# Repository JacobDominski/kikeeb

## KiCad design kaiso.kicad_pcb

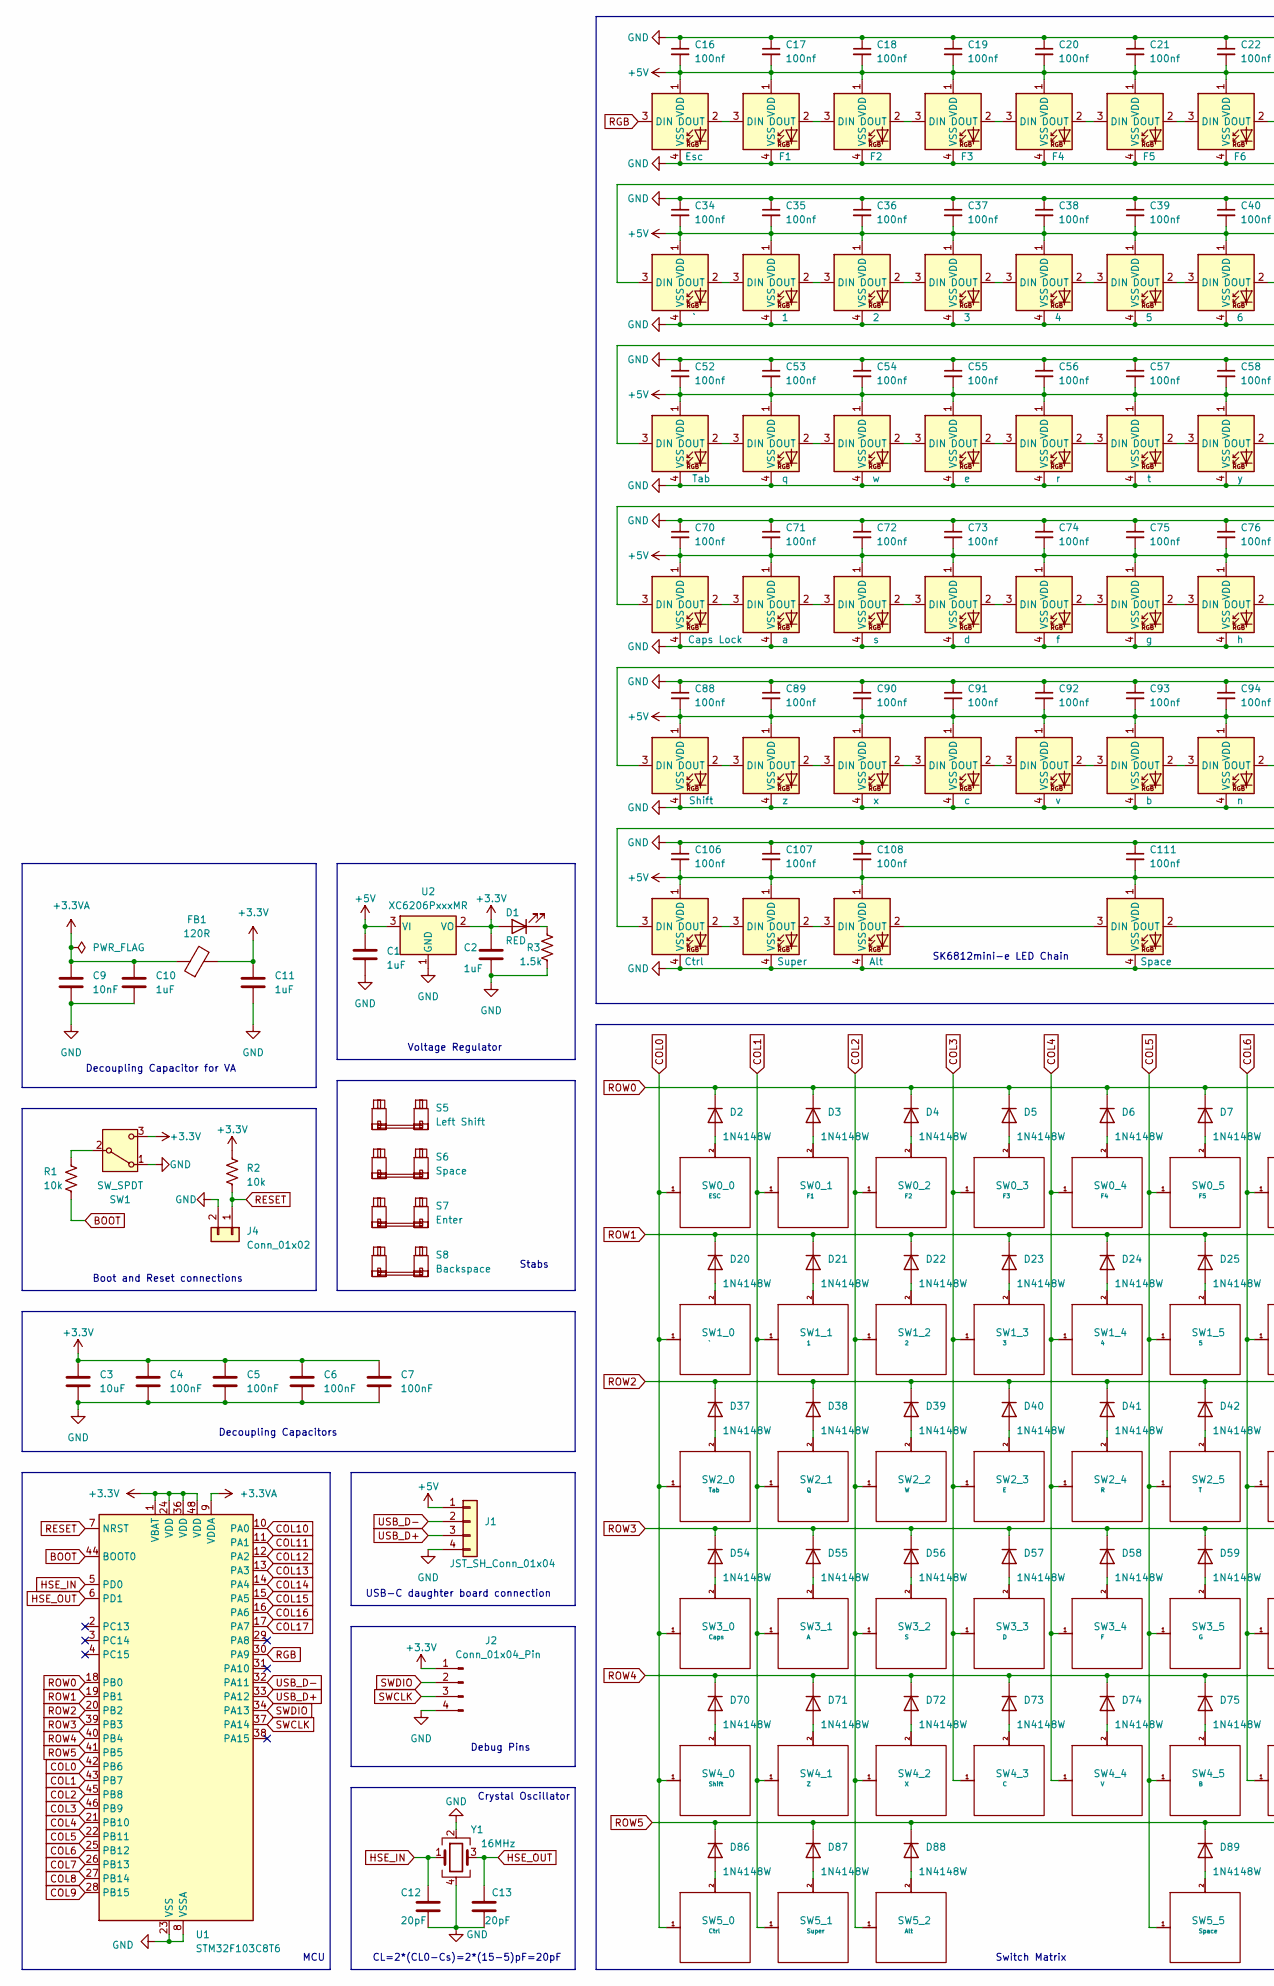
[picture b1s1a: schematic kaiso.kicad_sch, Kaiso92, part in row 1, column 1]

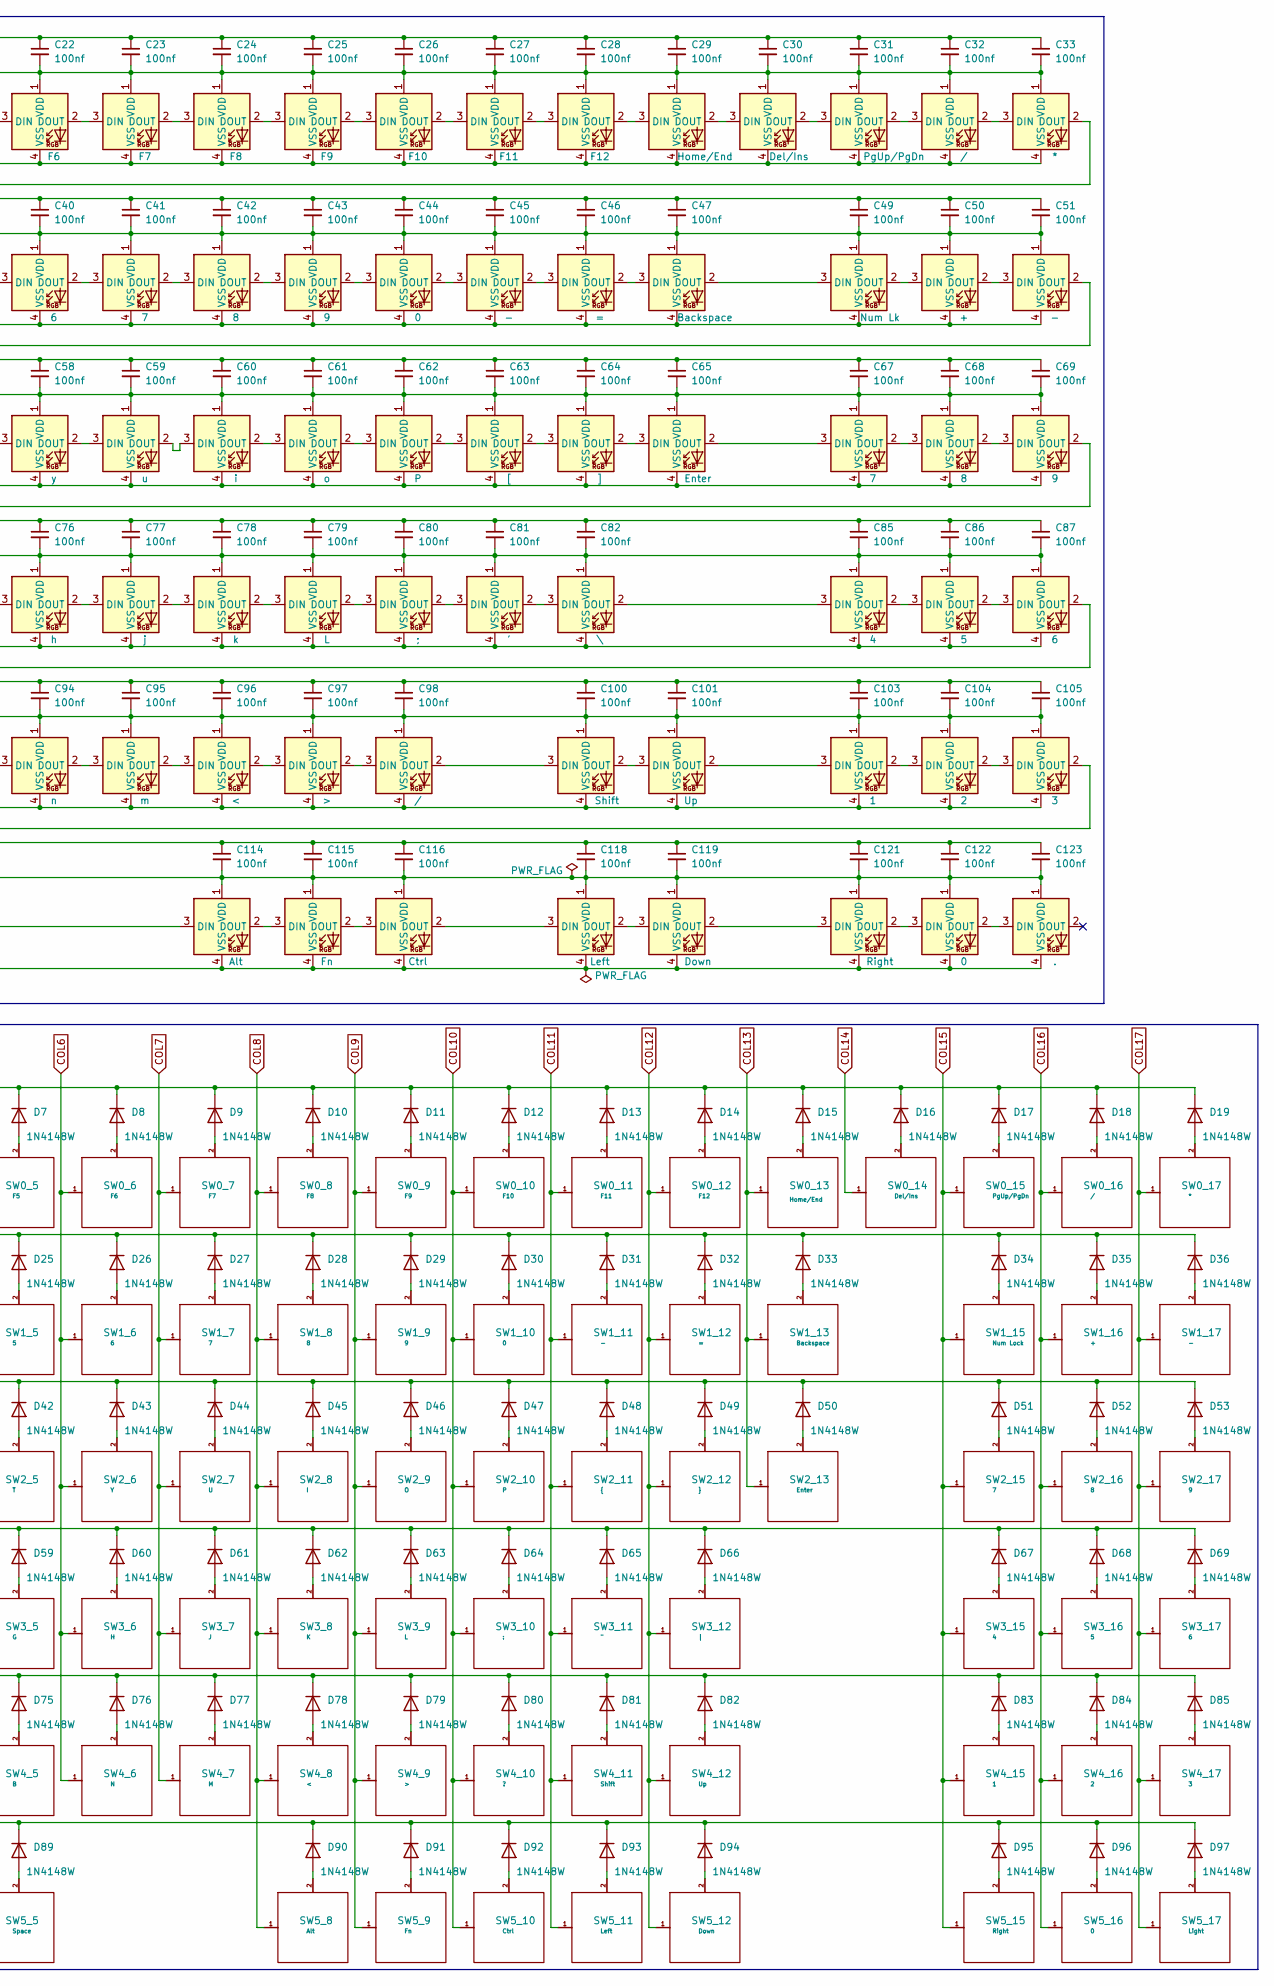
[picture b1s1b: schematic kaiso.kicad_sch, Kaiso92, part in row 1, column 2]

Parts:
C1, C2, C10, C11: 1uF; C_0402_1005Metric
C3: 10uF; C_0603_1608Metric
C4, C5, C6, C7: 100nF; C_0402_1005Metric
C9: 10nF; C_0603_1608Metric
C12, C13: 20pF; C_0201_0603Metric
C16, C17, C18, C19, C20, C21, C22, C23, C24, C25, C26, C27, C28, C29, C30, C31, C32, C33, C34, C35, C36, C37, C38, C39, C40, C41, C42, C43, C44, C45, C46, C47, C49, C50, C51, C52, C53, C54, C55, C56, C57, C58, C59, C60, C61, C62, C63, C64, C65, C67, C68, C69, C70, C71, C72, C73, C74, C75, C76, C77, C78, C79, C80, C81, C82, C85, C86, C87, C88, C89, C90, C91, C92, C93, C94, C95, C96, C97, C98, C100, C101, C103, C104, C105, C106, C107, C108, C111, C114, C115, C116, C118, C119, C121, C122, C123: 100nf; C_0402_1005Metric
D1: RED; LED_0603_1608Metric
D2, D3, D4, D5, D6, D7, D8, D9, D10, D11, D12, D13, D14, D15, D16, D17, D18, D19, D20, D21, D22, D23, D24, D25, D26, D27, D28, D29, D30, D31, D32, D33, D34, D35, D36, D37, D38, D39, D40, D41, D42, D43, D44, D45, D46, D47, D48, D49, D50, D51, D52, D53, D54, D55, D56, D57, D58, D59, D60, D61, D62, D63, D64, D65, D66, D67, D68, D69, D70, D71, D72, D73, D74, D75, D76, D77, D78, D79, D80, D81, D82, D83, D84, D85, D86, D87, D88, D89, D90, D91, D92, D93, D94, D95, D96, D97: 1N4148W; D_SOD-123
FB1: 120R; L_0603_1608Metric
J1: JST_SH_Conn_01x04; JST_SH_SM04B-SRSS-TB_1x04-1MP_P1.00mm_Horizontal
J2: Conn_01x04_Pin; PinHeader_1x04_P2.54mm_Vertical
J4: Conn_01x02; PinHeader_1x02_P2.54mm_Vertical
LED1: Esc; LED_MX_6028R
LED2: F1; LED_MX_6028R
LED3: F2; LED_MX_6028R
LED4: F3; LED_MX_6028R
LED5: F4; LED_MX_6028R
LED6: F5; LED_MX_6028R
LED7: F6; LED_MX_6028R
LED8: F7; LED_MX_6028R
LED9: F8; LED_MX_6028R
LED10: F9; LED_MX_6028R
LED11: F10; LED_MX_6028R
LED12: F11; LED_MX_6028R
LED13: F12; LED_MX_6028R
LED14: Home/End; LED_MX_6028R
LED15: Del/Ins; LED_MX_6028R
LED16: PgUp/PgDn; LED_MX_6028R
LED17, LED83: /; LED_MX_6028R
LED18: *; LED_MX_6028R
LED19: `; LED_MX_6028R
LED20, LED88: 1; LED_MX_6028R
LED21, LED89: 2; LED_MX_6028R
LED22, LED90: 3; LED_MX_6028R
LED23, LED70: 4; LED_MX_6028R
LED24, LED71: 5; LED_MX_6028R
LED25, LED72: 6; LED_MX_6028R
LED26, LED52: 7; LED_MX_6028R
LED27, LED53: 8; LED_MX_6028R
LED28, LED54: 9; LED_MX_6028R
LED29, LED107: 0; LED_MX_6028R
LED30, LED36: -; LED_MX_6028R
LED31: =; LED_MX_6028R
LED32: Backspace; LED_MX_6028R
LED34: Num Lk; LED_MX_6028R
LED35: +; LED_MX_6028R
LED37: Tab; LED_MX_6028R
LED38: q; LED_MX_6028R
LED39: w; LED_MX_6028R
LED40: e; LED_MX_6028R
LED41: r; LED_MX_6028R
LED42: t; LED_MX_6028R
LED43: y; LED_MX_6028R
LED44: u; LED_MX_6028R
LED45: i; LED_MX_6028R
LED46: o; LED_MX_6028R
LED47: P; LED_MX_6028R
LED48: [; LED_MX_6028R
LED49: ]; LED_MX_6028R
LED50: Enter; LED_MX_6028R
LED55: Caps Lock; LED_MX_6028R
LED56: a; LED_MX_6028R
LED57: s; LED_MX_6028R
LED58: d; LED_MX_6028R
LED59: f; LED_MX_6028R
LED60: g; LED_MX_6028R
LED61: h; LED_MX_6028R
LED62: j; LED_MX_6028R
LED63: k; LED_MX_6028R
LED64: L; LED_MX_6028R
LED65: ;; LED_MX_6028R
LED66: '; LED_MX_6028R
LED67: \; LED_MX_6028R
LED73, LED85: Shift; LED_MX_6028R
LED74: z; LED_MX_6028R
LED75: x; LED_MX_6028R
LED76: c; LED_MX_6028R
LED77: v; LED_MX_6028R
LED78: b; LED_MX_6028R
LED79: n; LED_MX_6028R
LED80: m; LED_MX_6028R
LED81: <; LED_MX_6028R
LED82: >; LED_MX_6028R
LED86: Up; LED_MX_6028R
LED91, LED101: Ctrl; LED_MX_6028R
LED92: Super; LED_MX_6028R
LED93, LED99: Alt; LED_MX_6028R
LED96: Space; LED_MX_6028R
LED100: Fn; LED_MX_6028R
LED103: Left; LED_MX_6028R
LED104: Down; LED_MX_6028R
LED106: Right; LED_MX_6028R
LED108: .; LED_MX_6028R
R1, R2: 10k; R_0402_1005Metric
R3: 1.5k; R_0402_1005Metric
S5: Left Shift; STAB_MX_2.25u
S6: Space; STAB_MX_6.25u
S7: Enter; STAB_MX_ISO
S8: Backspace; STAB_MX_2u
SW0_0, SW0_1, SW0_2, SW0_3, SW0_4, SW0_5, SW0_6, SW0_7, SW0_8, SW0_9, SW0_10, SW0_11, SW0_12, SW0_13, SW0_14, SW0_15, SW0_16, SW0_17, SW1_0, SW1_1, SW1_2, SW1_3, SW1_4, SW1_5, SW1_6, SW1_7, SW1_8, SW1_9, SW1_10, SW1_11, SW1_12, SW1_13, SW1_15, SW1_16, SW1_17, SW2_1, SW2_2, SW2_3, SW2_4, SW2_5, SW2_6, SW2_7, SW2_8, SW2_9, SW2_10, SW2_11, SW2_12, SW2_13, SW2_15, SW2_16, SW2_17, SW3_1, SW3_2, SW3_3, SW3_4, SW3_5, SW3_6, SW3_7, SW3_8, SW3_9, SW3_10, SW3_11, SW3_12, SW3_15, SW3_16, SW3_17, SW4_0, SW4_1, SW4_2, SW4_3, SW4_4, SW4_5, SW4_6, SW4_7, SW4_8, SW4_9, SW4_10, SW4_12, SW4_15, SW4_16, SW4_17, SW5_5, SW5_8, SW5_9, SW5_10, SW5_11, SW5_12, SW5_15, SW5_16, SW5_17: Mechanical_Switch; SW_MX_1u
SW1: SW_SPDT; SW_SPDT_PCM12
SW2_0: Mechanical_Switch; SW_MX_1.5u
SW3_0, SW4_11: Mechanical_Switch; SW_MX_1.75u
SW5_0, SW5_1, SW5_2: Mechanical_Switch; SW_MX_1.25u
U1: STM32F103C8T6; LQFP-48_7x7mm_P0.5mm
U2: XC6206PxxxMR; SOT-23-3
Y1: 16MHz; Resonator_SMD_Murata_CSTxExxV-3Pin_3.0x1.1mm

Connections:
+3.3V: C2.1, C3.1, C4.1, C5.1, C6.1, C7.1, C11.1, D1.2 (A), FB1.2, J2.1, R2.1, SW1.3 (C), U1.1 (VBAT), U1.24 (VDD), U1.36 (VDD), U1.48 (VDD), U2.2 (VO)
+3.3VA: C9.1, C10.1, FB1.1, U1.9 (VDDA)
+5V: C1.1, C16.2, C17.2, C18.2, C19.2, C20.2, C21.2, C22.2, C23.2, C24.2, C25.2, C26.2, C27.2, C28.2, C29.2, C30.2, C31.2, C32.2, C33.2, C34.2, C35.2, C36.2, C37.2, C38.2, C39.2, C40.2, C41.2, C42.2, C43.2, C44.2, C45.2, C46.2, C47.2, C49.2, C50.2, C51.2, C52.2, C53.2, C54.2, C55.2, C56.2, C57.2, C58.2, C59.2, C60.2, C61.2, C62.2, C63.2, C64.2, C65.2, C67.2, C68.2, C69.2, C70.2, C71.2, C72.2, C73.2, C74.2, C75.2, C76.2, C77.2, C78.2, C79.2, C80.2, C81.2, C82.2, C85.2, C86.2, C87.2, C88.2, C89.2, C90.2, C91.2, C92.2, C93.2, C94.2, C95.2, C96.2, C97.2, C98.2, C100.2, C101.2, C103.2, C104.2, C105.2, C106.2, C107.2, C108.2, C111.2, C114.2, C115.2, C116.2, C118.2, C119.2, C121.2, C122.2, C123.2, J1.1, LED1.1 (VDD), LED2.1 (VDD), LED3.1 (VDD), LED4.1 (VDD), LED5.1 (VDD), LED6.1 (VDD), LED7.1 (VDD), LED8.1 (VDD), LED9.1 (VDD), LED10.1 (VDD), LED11.1 (VDD), LED12.1 (VDD), LED13.1 (VDD), LED14.1 (VDD), LED15.1 (VDD), LED16.1 (VDD), LED17.1 (VDD), LED18.1 (VDD), LED19.1 (VDD), LED20.1 (VDD), LED21.1 (VDD), LED22.1 (VDD), LED23.1 (VDD), LED24.1 (VDD), LED25.1 (VDD), LED26.1 (VDD), LED27.1 (VDD), LED28.1 (VDD), LED29.1 (VDD), LED30.1 (VDD), LED31.1 (VDD), LED32.1 (VDD), LED34.1 (VDD), LED35.1 (VDD), LED36.1 (VDD), LED37.1 (VDD), LED38.1 (VDD), LED39.1 (VDD), LED40.1 (VDD), LED41.1 (VDD), LED42.1 (VDD), LED43.1 (VDD), LED44.1 (VDD), LED45.1 (VDD), LED46.1 (VDD), LED47.1 (VDD), LED48.1 (VDD), LED49.1 (VDD), LED50.1 (VDD), LED52.1 (VDD), LED53.1 (VDD), LED54.1 (VDD), LED55.1 (VDD), LED56.1 (VDD), LED57.1 (VDD), LED58.1 (VDD), LED59.1 (VDD), LED60.1 (VDD), LED61.1 (VDD), LED62.1 (VDD), LED63.1 (VDD), LED64.1 (VDD), LED65.1 (VDD), LED66.1 (VDD), LED67.1 (VDD), LED70.1 (VDD), LED71.1 (VDD), LED72.1 (VDD), LED73.1 (VDD), LED74.1 (VDD), LED75.1 (VDD), LED76.1 (VDD), LED77.1 (VDD), LED78.1 (VDD), LED79.1 (VDD), LED80.1 (VDD), LED81.1 (VDD), LED82.1 (VDD), LED83.1 (VDD), LED85.1 (VDD), LED86.1 (VDD), LED88.1 (VDD), LED89.1 (VDD), LED90.1 (VDD), LED91.1 (VDD), LED92.1 (VDD), LED93.1 (VDD), LED96.1 (VDD), LED99.1 (VDD), LED100.1 (VDD), LED101.1 (VDD), LED103.1 (VDD), LED104.1 (VDD), LED106.1 (VDD), LED107.1 (VDD), LED108.1 (VDD), U2.3 (VI)
BOOT: R1.2, U1.44 (BOOT0)
COL0: SW0_0.1, SW1_0.1, SW2_0.1, SW3_0.1, SW4_0.1, SW5_0.1, U1.42 (PB6)
COL1: SW0_1.1, SW1_1.1, SW2_1.1, SW3_1.1, SW4_1.1, SW5_1.1, U1.43 (PB7)
COL2: SW0_2.1, SW1_2.1, SW2_2.1, SW3_2.1, SW4_2.1, SW5_2.1, U1.45 (PB8)
COL3: SW0_3.1, SW1_3.1, SW2_3.1, SW3_3.1, SW4_3.1, U1.46 (PB9)
COL4: SW0_4.1, SW1_4.1, SW2_4.1, SW3_4.1, SW4_4.1, U1.21 (PB10)
COL5: SW0_5.1, SW1_5.1, SW2_5.1, SW3_5.1, SW4_5.1, SW5_5.1, U1.22 (PB11)
COL6: SW0_6.1, SW1_6.1, SW2_6.1, SW3_6.1, SW4_6.1, U1.25 (PB12)
COL7: SW0_7.1, SW1_7.1, SW2_7.1, SW3_7.1, SW4_7.1, U1.26 (PB13)
COL8: SW0_8.1, SW1_8.1, SW2_8.1, SW3_8.1, SW4_8.1, SW5_8.1, U1.27 (PB14)
COL9: SW0_9.1, SW1_9.1, SW2_9.1, SW3_9.1, SW4_9.1, SW5_9.1, U1.28 (PB15)
COL10: SW0_10.1, SW1_10.1, SW2_10.1, SW3_10.1, SW4_10.1, SW5_10.1, U1.10 (PA0)
COL11: SW0_11.1, SW1_11.1, SW2_11.1, SW3_11.1, SW4_11.1, SW5_11.1, U1.11 (PA1)
COL12: SW0_12.1, SW1_12.1, SW2_12.1, SW3_12.1, SW4_12.1, SW5_12.1, U1.12 (PA2)
COL13: SW0_13.1, SW1_13.1, SW2_13.1, U1.13 (PA3)
COL14: SW0_14.1, U1.14 (PA4)
COL15: SW0_15.1, SW1_15.1, SW2_15.1, SW3_15.1, SW4_15.1, SW5_15.1, U1.15 (PA5)
COL16: SW0_16.1, SW1_16.1, SW2_16.1, SW3_16.1, SW4_16.1, SW5_16.1, U1.16 (PA6)
COL17: SW0_17.1, SW1_17.1, SW2_17.1, SW3_17.1, SW4_17.1, SW5_17.1, U1.17 (PA7)
GND: C1.2, C2.2, C3.2, C4.2, C5.2, C6.2, C7.2, C9.2, C10.2, C11.2, C12.2, C13.2, C16.1, C17.1, C18.1, C19.1, C20.1, C21.1, C22.1, C23.1, C24.1, C25.1, C26.1, C27.1, C28.1, C29.1, C30.1, C31.1, C32.1, C33.1, C34.1, C35.1, C36.1, C37.1, C38.1, C39.1, C40.1, C41.1, C42.1, C43.1, C44.1, C45.1, C46.1, C47.1, C49.1, C50.1, C51.1, C52.1, C53.1, C54.1, C55.1, C56.1, C57.1, C58.1, C59.1, C60.1, C61.1, C62.1, C63.1, C64.1, C65.1, C67.1, C68.1, C69.1, C70.1, C71.1, C72.1, C73.1, C74.1, C75.1, C76.1, C77.1, C78.1, C79.1, C80.1, C81.1, C82.1, C85.1, C86.1, C87.1, C88.1, C89.1, C90.1, C91.1, C92.1, C93.1, C94.1, C95.1, C96.1, C97.1, C98.1, C100.1, C101.1, C103.1, C104.1, C105.1, C106.1, C107.1, C108.1, C111.1, C114.1, C115.1, C116.1, C118.1, C119.1, C121.1, C122.1, C123.1, J1.4, J2.4, J4.2, LED1.4 (VSS), LED2.4 (VSS), LED3.4 (VSS), LED4.4 (VSS), LED5.4 (VSS), LED6.4 (VSS), LED7.4 (VSS), LED8.4 (VSS), LED9.4 (VSS), LED10.4 (VSS), LED11.4 (VSS), LED12.4 (VSS), LED13.4 (VSS), LED14.4 (VSS), LED15.4 (VSS), LED16.4 (VSS), LED17.4 (VSS), LED18.4 (VSS), LED19.4 (VSS), LED20.4 (VSS), LED21.4 (VSS), LED22.4 (VSS), LED23.4 (VSS), LED24.4 (VSS), LED25.4 (VSS), LED26.4 (VSS), LED27.4 (VSS), LED28.4 (VSS), LED29.4 (VSS), LED30.4 (VSS), LED31.4 (VSS), LED32.4 (VSS), LED34.4 (VSS), LED35.4 (VSS), LED36.4 (VSS), LED37.4 (VSS), LED38.4 (VSS), LED39.4 (VSS), LED40.4 (VSS), LED41.4 (VSS), LED42.4 (VSS), LED43.4 (VSS), LED44.4 (VSS), LED45.4 (VSS), LED46.4 (VSS), LED47.4 (VSS), LED48.4 (VSS), LED49.4 (VSS), LED50.4 (VSS), LED52.4 (VSS), LED53.4 (VSS), LED54.4 (VSS), LED55.4 (VSS), LED56.4 (VSS), LED57.4 (VSS), LED58.4 (VSS), LED59.4 (VSS), LED60.4 (VSS), LED61.4 (VSS), LED62.4 (VSS), LED63.4 (VSS), LED64.4 (VSS), LED65.4 (VSS), LED66.4 (VSS), LED67.4 (VSS), LED70.4 (VSS), LED71.4 (VSS), LED72.4 (VSS), LED73.4 (VSS), LED74.4 (VSS), LED75.4 (VSS), LED76.4 (VSS), LED77.4 (VSS), LED78.4 (VSS), LED79.4 (VSS), LED80.4 (VSS), LED81.4 (VSS), LED82.4 (VSS), LED83.4 (VSS), LED85.4 (VSS), LED86.4 (VSS), LED88.4 (VSS), LED89.4 (VSS), LED90.4 (VSS), LED91.4 (VSS), LED92.4 (VSS), LED93.4 (VSS), LED96.4 (VSS), LED99.4 (VSS), LED100.4 (VSS), LED101.4 (VSS), LED103.4 (VSS), LED104.4 (VSS), LED106.4 (VSS), LED107.4 (VSS), LED108.4 (VSS), R3.2, SW1.1 (A), U1.8 (VSSA), U1.23 (VSS), U1.35 (VSS), U1.47 (VSS), U2.1 (GND), Y1.2, Y1.4
HSE_IN: C12.1, U1.5 (PD0), Y1.1
HSE_OUT: C13.1, U1.6 (PD1), Y1.3
unnamed: D1.1 (K), R3.1
unnamed: D2.2 (A), SW0_0.2
unnamed: D3.2 (A), SW0_1.2
unnamed: D4.2 (A), SW0_2.2
unnamed: D5.2 (A), SW0_3.2
unnamed: D6.2 (A), SW0_4.2
unnamed: D7.2 (A), SW0_5.2
unnamed: D8.2 (A), SW0_6.2
unnamed: D9.2 (A), SW0_7.2
unnamed: D10.2 (A), SW0_8.2
unnamed: D11.2 (A), SW0_9.2
unnamed: D12.2 (A), SW0_10.2
unnamed: D13.2 (A), SW0_11.2
unnamed: D14.2 (A), SW0_12.2
unnamed: D15.2 (A), SW0_13.2
unnamed: D16.2 (A), SW0_14.2
unnamed: D17.2 (A), SW0_15.2
unnamed: D18.2 (A), SW0_16.2
unnamed: D19.2 (A), SW0_17.2
unnamed: D20.2 (A), SW1_0.2
unnamed: D21.2 (A), SW1_1.2
unnamed: D22.2 (A), SW1_2.2
unnamed: D23.2 (A), SW1_3.2
unnamed: D24.2 (A), SW1_4.2
unnamed: D25.2 (A), SW1_5.2
unnamed: D26.2 (A), SW1_6.2
unnamed: D27.2 (A), SW1_7.2
unnamed: D28.2 (A), SW1_8.2
unnamed: D29.2 (A), SW1_9.2
unnamed: D30.2 (A), SW1_10.2
unnamed: D31.2 (A), SW1_11.2
unnamed: D32.2 (A), SW1_12.2
unnamed: D33.2 (A), SW1_13.2
unnamed: D34.2 (A), SW1_15.2
unnamed: D35.2 (A), SW1_16.2
unnamed: D36.2 (A), SW1_17.2
unnamed: D37.2 (A), SW2_0.2
unnamed: D38.2 (A), SW2_1.2
unnamed: D39.2 (A), SW2_2.2
unnamed: D40.2 (A), SW2_3.2
unnamed: D41.2 (A), SW2_4.2
unnamed: D42.2 (A), SW2_5.2
unnamed: D43.2 (A), SW2_6.2
unnamed: D44.2 (A), SW2_7.2
unnamed: D45.2 (A), SW2_8.2
unnamed: D46.2 (A), SW2_9.2
unnamed: D47.2 (A), SW2_10.2
unnamed: D48.2 (A), SW2_11.2
unnamed: D49.2 (A), SW2_12.2
unnamed: D50.2 (A), SW2_13.2
unnamed: D51.2 (A), SW2_15.2
unnamed: D52.2 (A), SW2_16.2
unnamed: D53.2 (A), SW2_17.2
unnamed: D54.2 (A), SW3_0.2
unnamed: D55.2 (A), SW3_1.2
unnamed: D56.2 (A), SW3_2.2
unnamed: D57.2 (A), SW3_3.2
unnamed: D58.2 (A), SW3_4.2
unnamed: D59.2 (A), SW3_5.2
unnamed: D60.2 (A), SW3_6.2
unnamed: D61.2 (A), SW3_7.2
unnamed: D62.2 (A), SW3_8.2
unnamed: D63.2 (A), SW3_9.2
unnamed: D64.2 (A), SW3_10.2
unnamed: D65.2 (A), SW3_11.2
unnamed: D66.2 (A), SW3_12.2
unnamed: D67.2 (A), SW3_15.2
unnamed: D68.2 (A), SW3_16.2
unnamed: D69.2 (A), SW3_17.2
unnamed: D70.2 (A), SW4_0.2
unnamed: D71.2 (A), SW4_1.2
unnamed: D72.2 (A), SW4_2.2
unnamed: D73.2 (A), SW4_3.2
unnamed: D74.2 (A), SW4_4.2
unnamed: D75.2 (A), SW4_5.2
unnamed: D76.2 (A), SW4_6.2
unnamed: D77.2 (A), SW4_7.2
unnamed: D78.2 (A), SW4_8.2
unnamed: D79.2 (A), SW4_9.2
unnamed: D80.2 (A), SW4_10.2
unnamed: D81.2 (A), SW4_11.2
unnamed: D82.2 (A), SW4_12.2
unnamed: D83.2 (A), SW4_15.2
unnamed: D84.2 (A), SW4_16.2
unnamed: D85.2 (A), SW4_17.2
unnamed: D86.2 (A), SW5_0.2
unnamed: D87.2 (A), SW5_1.2
unnamed: D88.2 (A), SW5_2.2
unnamed: D89.2 (A), SW5_5.2
unnamed: D90.2 (A), SW5_8.2
unnamed: D91.2 (A), SW5_9.2
unnamed: D92.2 (A), SW5_10.2
unnamed: D93.2 (A), SW5_11.2
unnamed: D94.2 (A), SW5_12.2
unnamed: D95.2 (A), SW5_15.2
unnamed: D96.2 (A), SW5_16.2
unnamed: D97.2 (A), SW5_17.2
unnamed: LED1.2 (DOUT), LED2.3 (DIN)
unnamed: LED2.2 (DOUT), LED3.3 (DIN)
unnamed: LED3.2 (DOUT), LED4.3 (DIN)
unnamed: LED4.2 (DOUT), LED5.3 (DIN)
unnamed: LED5.2 (DOUT), LED6.3 (DIN)
unnamed: LED6.2 (DOUT), LED7.3 (DIN)
unnamed: LED7.2 (DOUT), LED8.3 (DIN)
unnamed: LED8.2 (DOUT), LED9.3 (DIN)
unnamed: LED9.2 (DOUT), LED10.3 (DIN)
unnamed: LED10.2 (DOUT), LED11.3 (DIN)
unnamed: LED11.2 (DOUT), LED12.3 (DIN)
unnamed: LED12.2 (DOUT), LED13.3 (DIN)
unnamed: LED13.2 (DOUT), LED14.3 (DIN)
unnamed: LED14.2 (DOUT), LED15.3 (DIN)
unnamed: LED15.2 (DOUT), LED16.3 (DIN)
unnamed: LED16.2 (DOUT), LED17.3 (DIN)
unnamed: LED17.2 (DOUT), LED18.3 (DIN)
unnamed: LED18.2 (DOUT), LED19.3 (DIN)
unnamed: LED19.2 (DOUT), LED20.3 (DIN)
unnamed: LED20.2 (DOUT), LED21.3 (DIN)
unnamed: LED21.2 (DOUT), LED22.3 (DIN)
unnamed: LED22.2 (DOUT), LED23.3 (DIN)
unnamed: LED23.2 (DOUT), LED24.3 (DIN)
unnamed: LED24.2 (DOUT), LED25.3 (DIN)
unnamed: LED25.2 (DOUT), LED26.3 (DIN)
unnamed: LED26.2 (DOUT), LED27.3 (DIN)
unnamed: LED27.2 (DOUT), LED28.3 (DIN)
unnamed: LED28.2 (DOUT), LED29.3 (DIN)
unnamed: LED29.2 (DOUT), LED30.3 (DIN)
unnamed: LED30.2 (DOUT), LED31.3 (DIN)
unnamed: LED31.2 (DOUT), LED32.3 (DIN)
unnamed: LED32.2 (DOUT), LED34.3 (DIN)
unnamed: LED34.2 (DOUT), LED35.3 (DIN)
unnamed: LED35.2 (DOUT), LED36.3 (DIN)
unnamed: LED36.2 (DOUT), LED37.3 (DIN)
unnamed: LED37.2 (DOUT), LED38.3 (DIN)
unnamed: LED38.2 (DOUT), LED39.3 (DIN)
unnamed: LED39.2 (DOUT), LED40.3 (DIN)
unnamed: LED40.2 (DOUT), LED41.3 (DIN)
unnamed: LED41.2 (DOUT), LED42.3 (DIN)
unnamed: LED42.2 (DOUT), LED43.3 (DIN)
unnamed: LED43.2 (DOUT), LED44.3 (DIN)
unnamed: LED44.2 (DOUT), LED45.3 (DIN)
unnamed: LED45.2 (DOUT), LED46.3 (DIN)
unnamed: LED46.2 (DOUT), LED47.3 (DIN)
unnamed: LED47.2 (DOUT), LED48.3 (DIN)
unnamed: LED48.2 (DOUT), LED49.3 (DIN)
unnamed: LED49.2 (DOUT), LED50.3 (DIN)
unnamed: LED50.2 (DOUT), LED52.3 (DIN)
unnamed: LED52.2 (DOUT), LED53.3 (DIN)
unnamed: LED53.2 (DOUT), LED54.3 (DIN)
unnamed: LED54.2 (DOUT), LED55.3 (DIN)
unnamed: LED55.2 (DOUT), LED56.3 (DIN)
unnamed: LED56.2 (DOUT), LED57.3 (DIN)
unnamed: LED57.2 (DOUT), LED58.3 (DIN)
unnamed: LED58.2 (DOUT), LED59.3 (DIN)
unnamed: LED59.2 (DOUT), LED60.3 (DIN)
unnamed: LED60.2 (DOUT), LED61.3 (DIN)
unnamed: LED61.2 (DOUT), LED62.3 (DIN)
unnamed: LED62.2 (DOUT), LED63.3 (DIN)
unnamed: LED63.2 (DOUT), LED64.3 (DIN)
unnamed: LED64.2 (DOUT), LED65.3 (DIN)
unnamed: LED65.2 (DOUT), LED66.3 (DIN)
unnamed: LED66.2 (DOUT), LED67.3 (DIN)
unnamed: LED67.2 (DOUT), LED70.3 (DIN)
unnamed: LED70.2 (DOUT), LED71.3 (DIN)
unnamed: LED71.2 (DOUT), LED72.3 (DIN)
unnamed: LED72.2 (DOUT), LED73.3 (DIN)
unnamed: LED73.2 (DOUT), LED74.3 (DIN)
unnamed: LED74.2 (DOUT), LED75.3 (DIN)
unnamed: LED75.2 (DOUT), LED76.3 (DIN)
unnamed: LED76.2 (DOUT), LED77.3 (DIN)
unnamed: LED77.2 (DOUT), LED78.3 (DIN)
unnamed: LED78.2 (DOUT), LED79.3 (DIN)
unnamed: LED79.2 (DOUT), LED80.3 (DIN)
unnamed: LED80.2 (DOUT), LED81.3 (DIN)
unnamed: LED81.2 (DOUT), LED82.3 (DIN)
unnamed: LED82.2 (DOUT), LED83.3 (DIN)
unnamed: LED83.2 (DOUT), LED85.3 (DIN)
unnamed: LED85.2 (DOUT), LED86.3 (DIN)
unnamed: LED86.2 (DOUT), LED88.3 (DIN)
unnamed: LED88.2 (DOUT), LED89.3 (DIN)
unnamed: LED89.2 (DOUT), LED90.3 (DIN)
unnamed: LED90.2 (DOUT), LED91.3 (DIN)
unnamed: LED91.2 (DOUT), LED92.3 (DIN)
unnamed: LED92.2 (DOUT), LED93.3 (DIN)
unnamed: LED93.2 (DOUT), LED96.3 (DIN)
unnamed: LED96.2 (DOUT), LED99.3 (DIN)
unnamed: LED99.2 (DOUT), LED100.3 (DIN)
unnamed: LED100.2 (DOUT), LED101.3 (DIN)
unnamed: LED101.2 (DOUT), LED103.3 (DIN)
unnamed: LED103.2 (DOUT), LED104.3 (DIN)
unnamed: LED104.2 (DOUT), LED106.3 (DIN)
unnamed: LED106.2 (DOUT), LED107.3 (DIN)
unnamed: LED107.2 (DOUT), LED108.3 (DIN)
unnamed: R1.1, SW1.2 (B)
RESET: J4.1, R2.2, U1.7 (NRST)
RGB: LED1.3 (DIN), U1.30 (PA9)
ROW0: D2.1 (K), D3.1 (K), D4.1 (K), D5.1 (K), D6.1 (K), D7.1 (K), D8.1 (K), D9.1 (K), D10.1 (K), D11.1 (K), D12.1 (K), D13.1 (K), D14.1 (K), D15.1 (K), D16.1 (K), D17.1 (K), D18.1 (K), D19.1 (K), U1.18 (PB0)
ROW1: D20.1 (K), D21.1 (K), D22.1 (K), D23.1 (K), D24.1 (K), D25.1 (K), D26.1 (K), D27.1 (K), D28.1 (K), D29.1 (K), D30.1 (K), D31.1 (K), D32.1 (K), D33.1 (K), D34.1 (K), D35.1 (K), D36.1 (K), U1.19 (PB1)
ROW2: D37.1 (K), D38.1 (K), D39.1 (K), D40.1 (K), D41.1 (K), D42.1 (K), D43.1 (K), D44.1 (K), D45.1 (K), D46.1 (K), D47.1 (K), D48.1 (K), D49.1 (K), D50.1 (K), D51.1 (K), D52.1 (K), D53.1 (K), U1.20 (PB2)
ROW3: D54.1 (K), D55.1 (K), D56.1 (K), D57.1 (K), D58.1 (K), D59.1 (K), D60.1 (K), D61.1 (K), D62.1 (K), D63.1 (K), D64.1 (K), D65.1 (K), D66.1 (K), D67.1 (K), D68.1 (K), D69.1 (K), U1.39 (PB3)
ROW4: D70.1 (K), D71.1 (K), D72.1 (K), D73.1 (K), D74.1 (K), D75.1 (K), D76.1 (K), D77.1 (K), D78.1 (K), D79.1 (K), D80.1 (K), D81.1 (K), D82.1 (K), D83.1 (K), D84.1 (K), D85.1 (K), U1.40 (PB4)
ROW5: D86.1 (K), D87.1 (K), D88.1 (K), D89.1 (K), D90.1 (K), D91.1 (K), D92.1 (K), D93.1 (K), D94.1 (K), D95.1 (K), D96.1 (K), D97.1 (K), U1.41 (PB5)
SWCLK: J2.3, U1.37 (PA14)
SWDIO: J2.2, U1.34 (PA13)
USB_D+: J1.3, U1.33 (PA12)
USB_D-: J1.2, U1.32 (PA11)

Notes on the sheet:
SK6812mini-e LED Chain
Voltage Regulator
MCU
Crystal Oscillator
Stabs
Decoupling Capacitors
Decoupling Capacitor for VA
USB-C daughter board connection
Debug Pins
Switch Matrix
Boot and Reset connections
CL=2*(CL0-Cs)=2*(15-5)pF=20pF

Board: 2 copper layers, 412 parts (0 on the bottom side), 230 nets, no tracks yet.

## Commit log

2024-03-07 Close to completion
    Schematic mostly done. I have both the led matrix and led daisy chain but have not decided which one to use. An external oscillator is not in the schematic but I might add one.
2024-03-31 Finished the schematic REV 1
    Still need to update the switch schematic symbol and double check the boot and reset pins
2024-03-31 updated the switch matrix symbols and fixed some violations.
2024-04-03 updated footprints
    Updated SPDT sch and finished adding all the footprints to all the sch symbols. Everything's good to move to the PCB editor.
2024-04-11 started the PCB design
    layout complete with switches. still need to figure out how to route it.
2024-04-12 added keyboard layout json file
2024-04-18 added the LEDs to the PCB and major components
    the USB-C, MCU, Crystal OSC, Caps, Volt Reg, Debug, and Boot pins have been added to a spot on the PCB. Last step is to add the caps and diodes to the LEDs and switches.
2024-04-18 added PNG files of the schematics and PCB.
